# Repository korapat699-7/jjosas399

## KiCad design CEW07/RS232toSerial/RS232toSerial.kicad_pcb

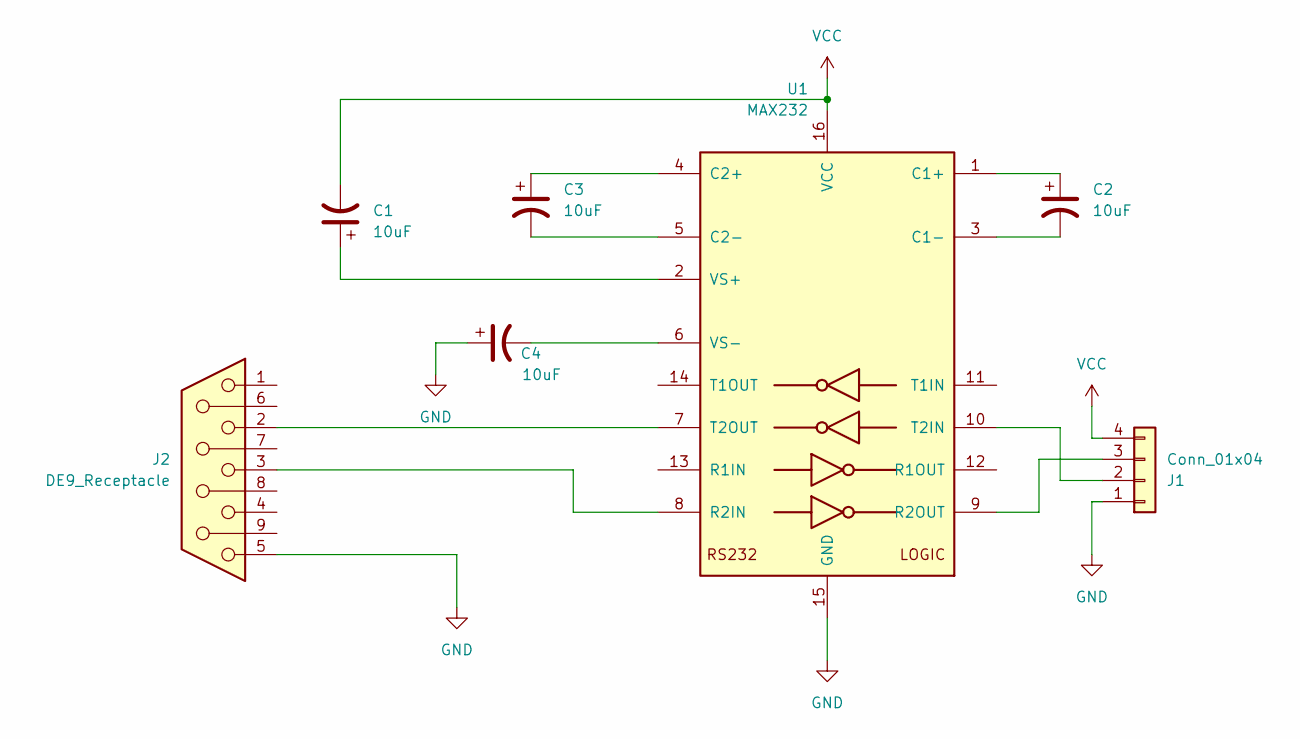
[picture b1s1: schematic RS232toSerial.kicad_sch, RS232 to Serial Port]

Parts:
C1, C2, C3, C4: 10uF; CP_Radial_D5.0mm_P2.50mm
J1: Conn_01x04; PinHeader_1x04_P2.54mm_Vertical
J2: DE9_Receptacle; DSUB-9_Female_Horizontal_P2.77x2.84mm_EdgePinOffset7.70mm_H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
U1: MAX232; DIP-16_W7.62mm

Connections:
GND: C4.1, J1.1, J2.5, U1.15 (GND)
unnamed: J1.2, U1.10 (T2IN)
unnamed: J1.3, U1.9 (R2OUT)
unnamed: C2.1, U1.1 (C1+)
unnamed: C2.2, U1.3 (C1-)
unnamed: C3.1, U1.4 (C2+)
unnamed: C3.2, U1.5 (C2-)
unnamed: J2.3, U1.8 (R2IN)
unnamed: J2.2, U1.7 (T2OUT)
unnamed: C1.1, U1.2 (VS+)
unnamed: C4.2, U1.6 (VS-)
VCC: C1.2, J1.4, U1.16 (VCC)

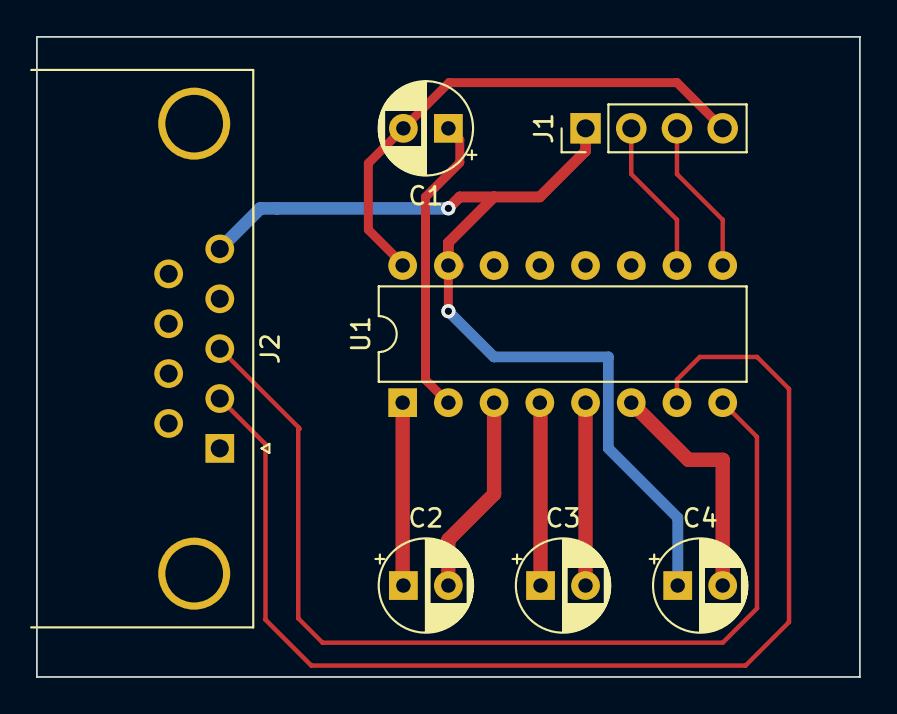
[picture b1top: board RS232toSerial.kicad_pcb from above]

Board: 2 copper layers, 45.7 x 35.6 mm, 7 parts (0 on the bottom side), 12 nets.

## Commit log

2023-11-15 add CEW07
